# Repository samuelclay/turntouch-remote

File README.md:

# Turn Touch remote firmware, schematic, and board layout
> The design files used for the nrf51-based Turn Touch remote.

<a href="https://turntouch.com"><br />Available at turntouch.com</a>

[![License][license-image]][license-url]

## Screenshots of the board design files

| PCB | EAGLE |
|:---:|:---:|
|  |  |

| Top | Bottom |
|:---:|:---:|
|  |  |

## Background

You can read the complete documentation and background on the [Turn Touch blog series](http://ofbrooklyn.com/2019/01/3/building-turntouch/#firmware).

## Features of the remote

[Turn Touch](https://turntouch.com) is a smart home remote control carved out of beautiful mahogany wood. This is a remote control for Hue lights, Sonos speakers, and all the other connected devices in your home. Turn Touch works on iOS and macOS, giving you control of your music, videos, presentations, and more. 

- [x] **Extraordinary design**: This isn't yet another plastic remote. Turn Touch is carved from solid wood and worked to a show-stopping, textured finish. 
- [x] **Well connected**: Turn Touch connects to most smart devices in your home that speak WiFi. And this is just the first version. Over time, there's no telling what you'll be able to control.
- [x] **Always ready**: Turn Touch is always on, always connected, and always ready to take your breath away. Once you connect your Turn Touch via Bluetooth it stays connected and always available, even without the Turn Touch app actively running. And there's no delay, when you press a button the result is instant.
- [x] **Built to last**: Not only will your Turn Touch stand up to drops and shock — its entire circuit board can be inexpensively replaced with newer, future wireless tech. You won't have to buy a new remote every time Apple comes out with a new phone. And instead of flimsy plastic clasps, a set of 8 strong magnets invisibly hold the remote together. 

## Requirements

- macOS or Windows
- nrf51 Development Kit ([$39 on Digikey](https://www.digikey.com/product-detail/en/nordic-semiconductor-asa/NRF51-DK/1490-1038-ND/5022449))
- EAGLE for schematic and board layout
- ARM toolchain for firmware

## Installation

To install dependencies, start here:

    https://devzone.nordicsemi.com/blogs/22/getting-started-with-nrf51-development-on-mac-os-x/

To use gcc, you will need to download:

 * nRF51 SDK
 * S110 SoftDevice
 * J-Link by Segger
 * srec_cat

    ```$ brew install srecord```

 * GCC ARM Embedded

    When installing GCC tools, do not use "The Unarchiver". It messes up the symlinks for
    all of the binaries. Make sure to use "Archive Utility"
    ```
    $ mv -f ~/Downloads/gcc-arm-none-eabi-4_9-2015q2 ~/projects/code/
    $ ln -s ~/projects/code/gcc-arm-none-eabi-4_9-2015q2 /usr/local/gcc-arm-none-eabi-4_9-2015q2
    ```

 * ./bin/nrfjprog.sh into /usr/local/bin/nrfjprog

### Running

    $ make
    $ make bootloader
    $ make flash
    $ ./bin/nrfjprog.sh --rtt

### Build on Windows

#### Build DFU package

    $ C:\Keil_v5\ARM\ARMCC\bin\fromelf.exe --bin --output Z:\remote\ble_peripheral\ble_app_template\pca10028\s110\arm5\_build\nrf51422_xxac_s110.bin Z:\remote\ble_peripheral\ble_app_template\pca10028\s110\arm5\_build\nrf51422_xxac_s110.axf

    $ & 'C:\Program Files (x86)\Nordic Semiconductor\Master Control Panel\3.10.0.14\nrf\nrfutil.exe' dfu genpkg --sd-req 0xfffe --application Z:\remote\ble_peripheral\ble_app_template\pca10028\s110\arm5\_build\nrf51422_xxac_s110.bin --application-version 0x06 --dev-revision 0x01 Z:\remote\ble_peripheral\nrf51_06.zip

##### Back on Mac

    $ cp ../ble_peripheral/nrf51_*.zip ../../app/Turn\ Touch\ Mac/DFU/firmwares/
    $ cp ../ble_peripheral/nrf51_*.zip ../../ios/Turn\ Touch\ iOS/DFU/

##### In Xcode (in both turntouch-mac/turntouch-ios repos)

In Supporting Files/defaults.plist, change `TT:firmware:version`

#### Build flash hex

    $ mergehex -m Z:/remote/firmware/libs/components/softdevice/s110/hex/s110_nrf51_8.0.0_softdevice.hex Z:/remote/ble_peripheral/dfu/bootloader/pca10028/dual_bank_ble_s110/arm5/_build/nrf51422_xxac.hex Z:/remote/ble_peripheral/ble_app_template/pca10028/s110/arm5/_build/nrf51422_xxac_s110.hex -o Z:/remote/ble_peripheral/nrf51_sd_bootloader_app.hex

#### `make flashwin` on Mac in firmware/

### Upgrading to latest nrf51 SDK

 1) Replace app_error.c with RTT logs
 2) Add BSP_BUTTON_ACTION_LONG_PUSH and BSP_BUTTON_ACTION_RELEASE to bsp.c

## Contribute

We would love you for the contribution to the **Turn Touch remote firmware**. Feel free to submit a Pull Request with the improvements or additions you've made.

## Turn Touch open source repositories and documentation

Everything about Turn Touch is open source and well documented. Here are all of Turn Touch's repos:

* [Turn Touch Mac OS app](https://github.com/samuelclay/turntouch-mac/)
* [Turn Touch iOS app](https://github.com/samuelclay/turntouch-ios/)
* [Turn Touch remote firmware and board layout](https://github.com/samuelclay/turntouch-remote/)
* [Turn Touch enclosure, CAD, and CAM](https://github.com/samuelclay/turntouch-enclosure/)

The entire Turn Touch build process is also documented:
* <a href="http://ofbrooklyn.com/2019/01/3/building-turntouch/">Everything you need to build your own Turn Touch smart remote<br /></a>
* <a href="http://ofbrooklyn.com/2019/01/3/building-turntouch/#firmware">Step one: Laying out the buttons and writing the firmware <br /></a>
* <a href="http://ofbrooklyn.com/2019/01/3/building-turntouch/#cad">Step two: Designing the remote to have perfect button clicks <br /></a>
* <a href="http://ofbrooklyn.com/2019/01/3/building-turntouch/#cnc">Step three: CNC machining and fixturing to accurately cut wood <br /></a>
* <a href="http://ofbrooklyn.com/2019/01/3/building-turntouch/#laser">Step four: Inlaying the mother of pearl <br /></a>

## Author

Samuel Clay – [@samuelclay](https://twitter.com/samuelclay) – [samuelclay.com](http://samuelclay.com)

Distributed under the MIT license. See ``LICENSE`` for more information.

[https://github.com/samuelclay/turntouch-mac](https://github.com/samuelclay)

[swift-image]:https://img.shields.io/badge/swift-3.0-orange.svg
[swift-url]: https://swift.org/
[license-image]: https://img.shields.io/badge/License-MIT-blue.svg
[license-url]: LICENSE
[travis-image]: https://img.shields.io/travis/dbader/node-datadog-metrics/master.svg?style=flat-square
[travis-url]: https://travis-ci.org/dbader/node-datadog-metrics
[codebeat-image]: https://codebeat.co/badges/c19b47ea-2f9d-45df-8458-b2d952fe9dad
[codebeat-url]: https://codebeat.co/projects/github-com-vsouza-awesomeios-com

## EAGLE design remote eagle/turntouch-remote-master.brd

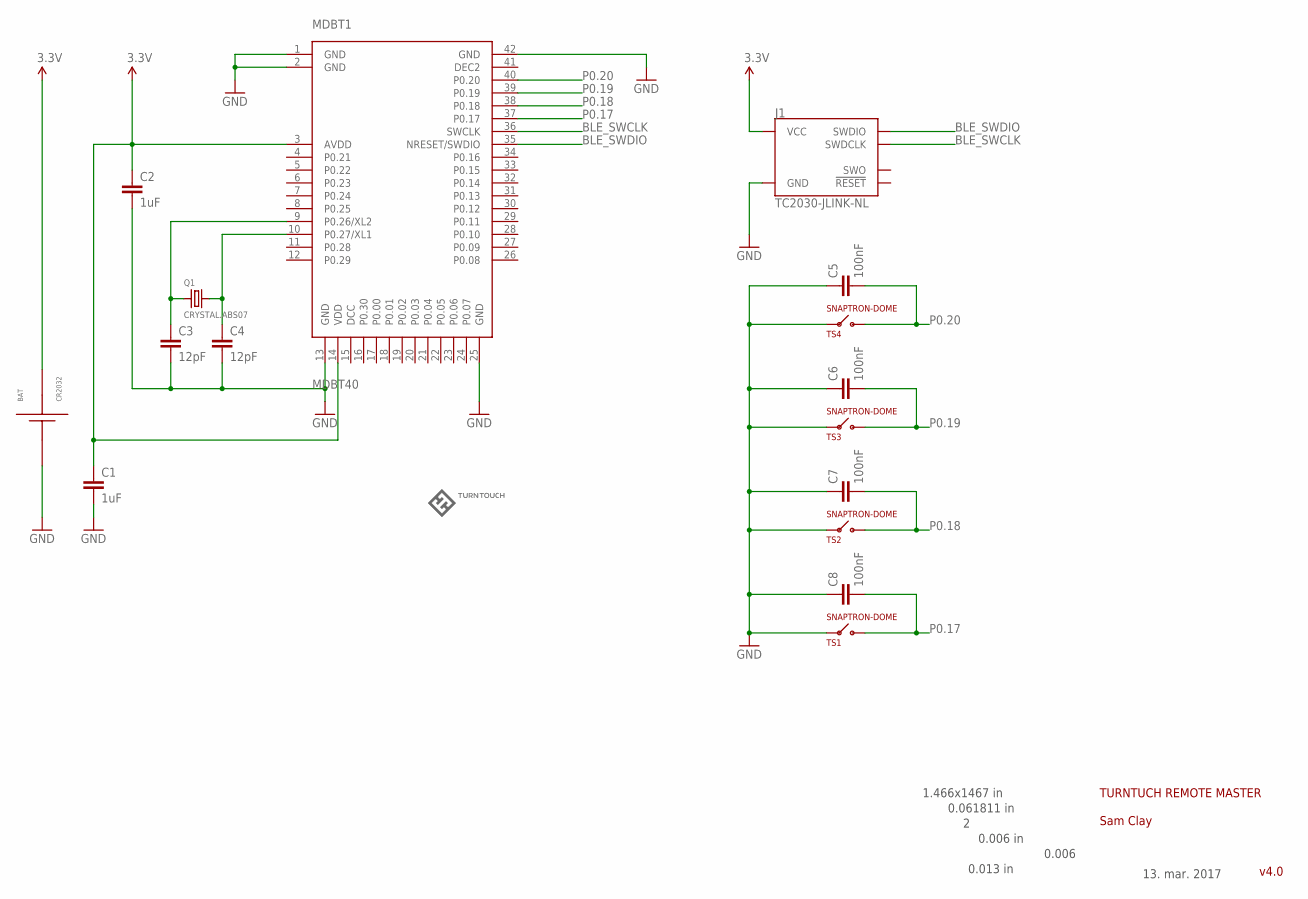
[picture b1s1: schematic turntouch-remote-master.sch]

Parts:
BAT: CR2032
C1, C2: 1uF; 0603-CAP
C3, C4: 12pF; 0603-CAP
C5, C6, C7, C8: 100nF; 0603-CAP
J1: TC2030-JLINK-NL; TC2030-IDC-NL
LOGO: TURNTOUCHLOGO200DPI; LOGO
MDBT1: MDBT40
Q1: CRYSTAL.ABS07; ABS07
TS1, TS2, TS3, TS4: SNAPTRON-DOME; DOME-M-SERIES

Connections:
3.3V: BAT.P$1 (VBAT), BAT.P$2 (VBAT), C1.1, C2.1, J1.1 (VCC), MDBT1.3 (AVDD), MDBT1.14 (VDD)
BLE_SWCLK: J1.4 (SWDCLK), MDBT1.36 (SWCLK)
BLE_SWDIO: J1.2 (SWDIO), MDBT1.35 (NRESET/SWDIO)
C5: C4.1, MDBT1.10 (P0.27/XL1), Q1.2
GND: BAT.GND, C1.2, C2.2, C3.2, C4.2, C5.1, C6.1, C7.1, C8.1, J1.5 (GND), MDBT1.1 (GND), MDBT1.2 (GND), MDBT1.13 (GND), MDBT1.25 (GND), MDBT1.42 (GND), TS1.P$1 (V), TS1.P$2 (V), TS2.P$1 (V), TS2.P$2 (V), TS3.P$1 (V), TS3.P$2 (V), TS4.P$1 (V), TS4.P$2 (V)
unnamed: C3.1, MDBT1.9 (P0.26/XL2), Q1.1
P0.17: C8.2, MDBT1.37 (P0.17), TS1.P$3 (B)
P0.18: C7.2, MDBT1.38 (P0.18), TS2.P$3 (B)
P0.19: C6.2, MDBT1.39 (P0.19), TS3.P$3 (B)
P0.20: C5.2, MDBT1.40 (P0.20), TS4.P$3 (B)

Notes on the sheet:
1.466x1467 in
0.061811 in
0.006 in
0.006
0.013 in
TURNTUCH REMOTE MASTER
v4.0
13. mar. 2017
Sam Clay

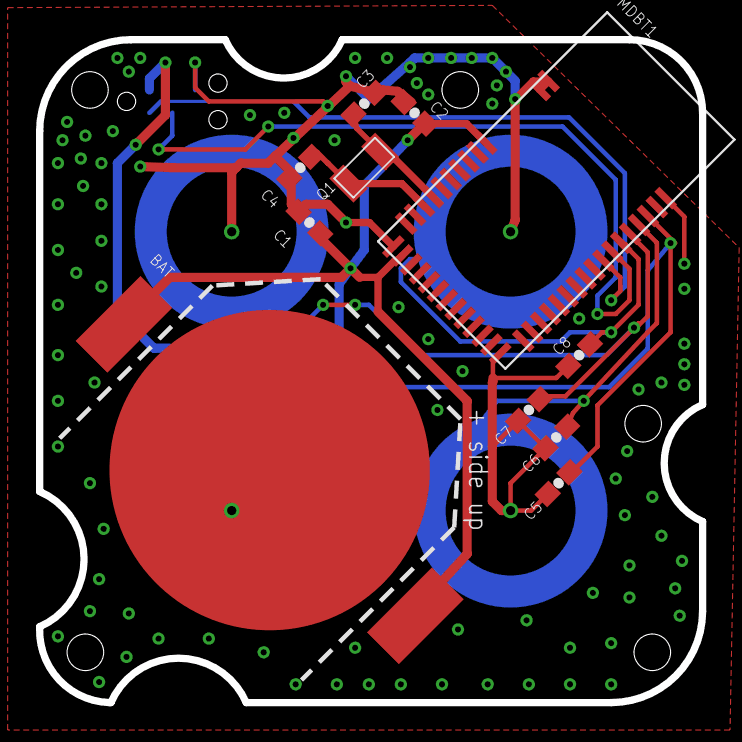
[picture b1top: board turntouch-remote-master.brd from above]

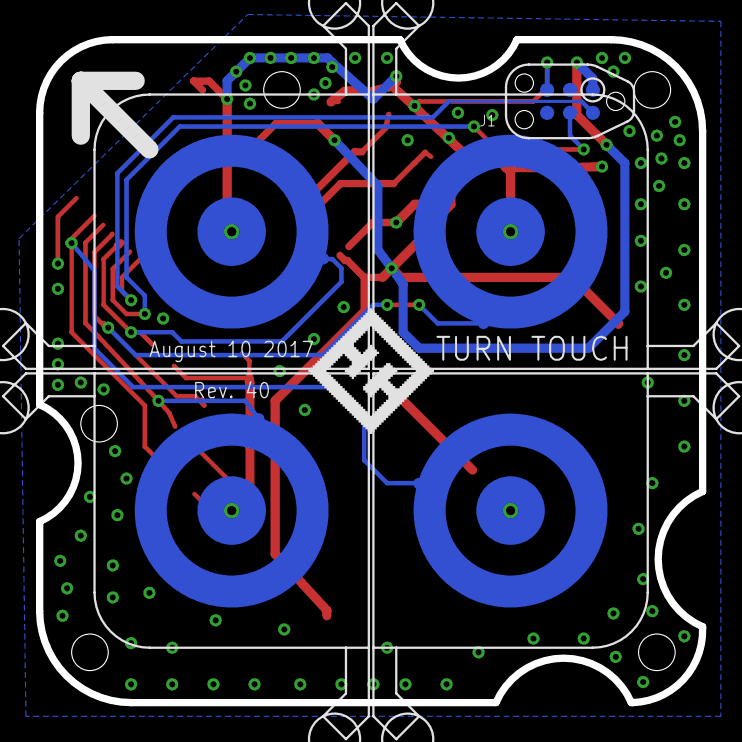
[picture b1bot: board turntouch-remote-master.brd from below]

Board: 2 copper layers, 36.8 x 36.8 mm, 17 parts (6 on the bottom side), 10 nets.

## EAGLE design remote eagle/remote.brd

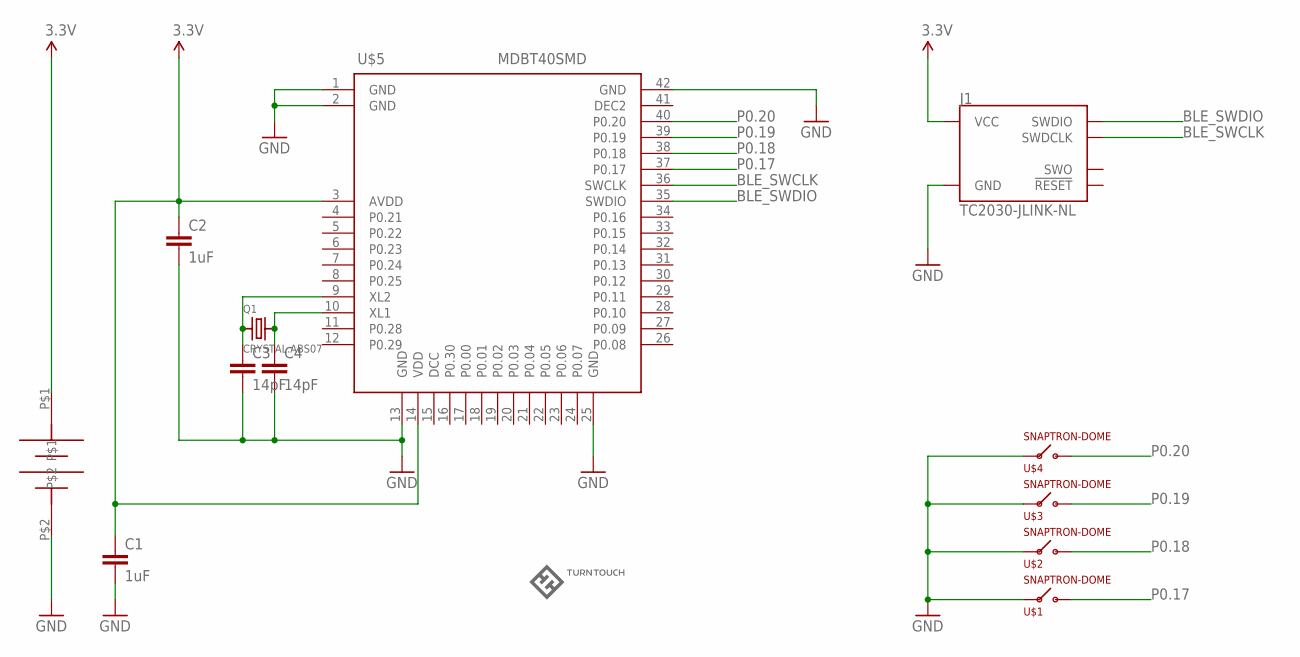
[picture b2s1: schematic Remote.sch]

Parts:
C1, C2: 1uF; 0603-CAP
C3, C4: 14pF; 0603-CAP
J1: TC2030-JLINK-NL; TC2030-IDC-NL
LOGO: TURNTOUCHLOGO200DPI; LOGO
Q1: CRYSTAL.ABS07; ABS07
U$1, U$2, U$3, U$4: SNAPTRON-DOME; DOME-M-SERIES
U$5: MDBT40SMD; MDBT40
U$6: COINCELLHOLDER; 20MMCOINCELL

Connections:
3.3V: C1.1, C2.1, J1.1 (VCC), U$5.3 (AVDD), U$5.14 (VDD), U$6.P$1
BLE_SWCLK: J1.4 (SWDCLK), U$5.36 (SWCLK)
BLE_SWDIO: J1.2 (SWDIO), U$5.35 (SWDIO)
C5: C4.1, Q1.2, U$5.10 (XL1)
GND: C1.2, C2.2, C3.2, C4.2, J1.5 (GND), U$1.P$1 (V), U$1.P$2 (V), U$2.P$1 (V), U$2.P$2 (V), U$3.P$1 (V), U$3.P$2 (V), U$4.P$1 (V), U$4.P$2 (V), U$5.1 (GND), U$5.2 (GND), U$5.13 (GND), U$5.25 (GND), U$5.42 (GND), U$6.P$2
unnamed: C3.1, Q1.1, U$5.9 (XL2)
P0.17: U$1.P$3 (B), U$5.37 (P0.17)
P0.18: U$2.P$3 (B), U$5.38 (P0.18)
P0.19: U$3.P$3 (B), U$5.39 (P0.19)
P0.20: U$4.P$3 (B), U$5.40 (P0.20)

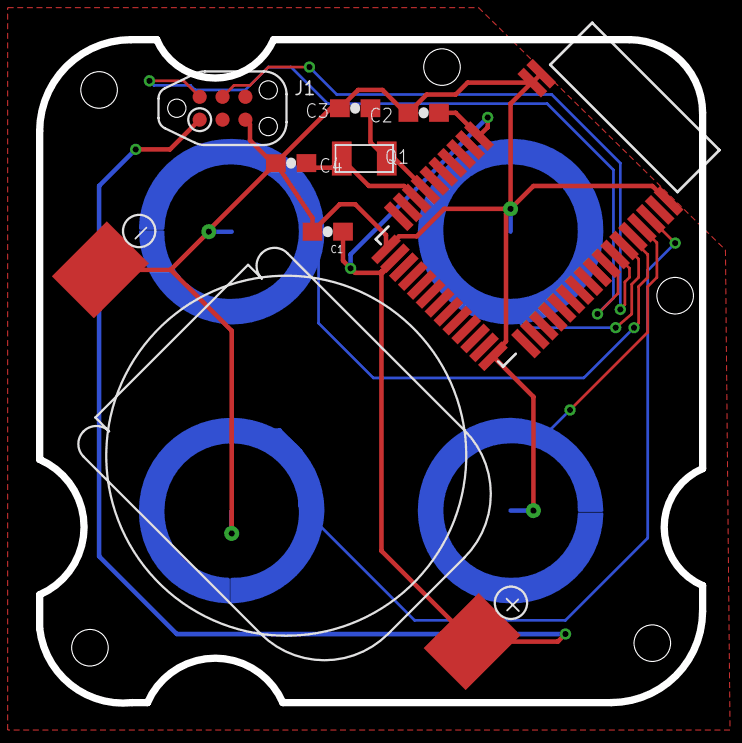
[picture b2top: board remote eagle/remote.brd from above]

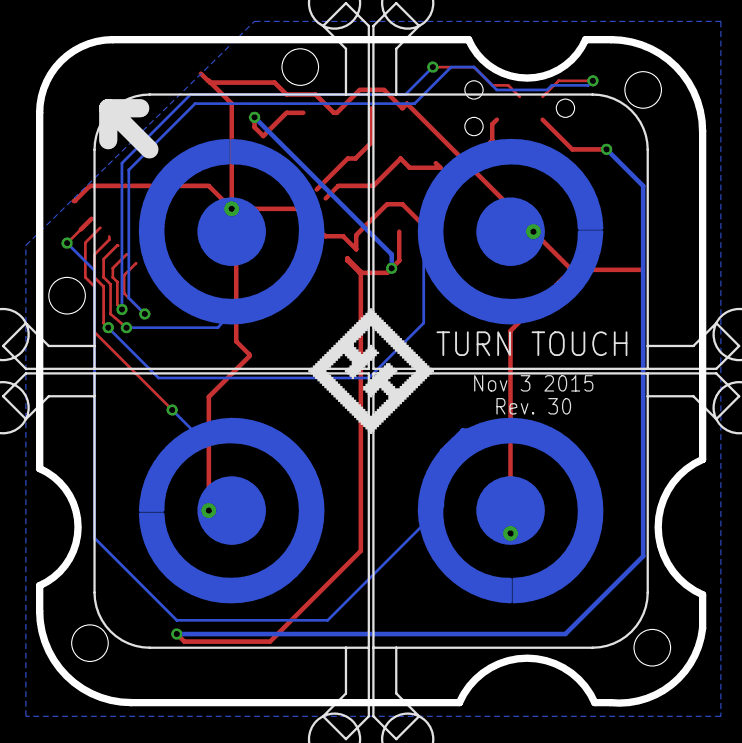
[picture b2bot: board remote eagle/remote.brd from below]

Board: 2 copper layers, 36.8 x 36.9 mm, 13 parts (5 on the bottom side), 10 nets.

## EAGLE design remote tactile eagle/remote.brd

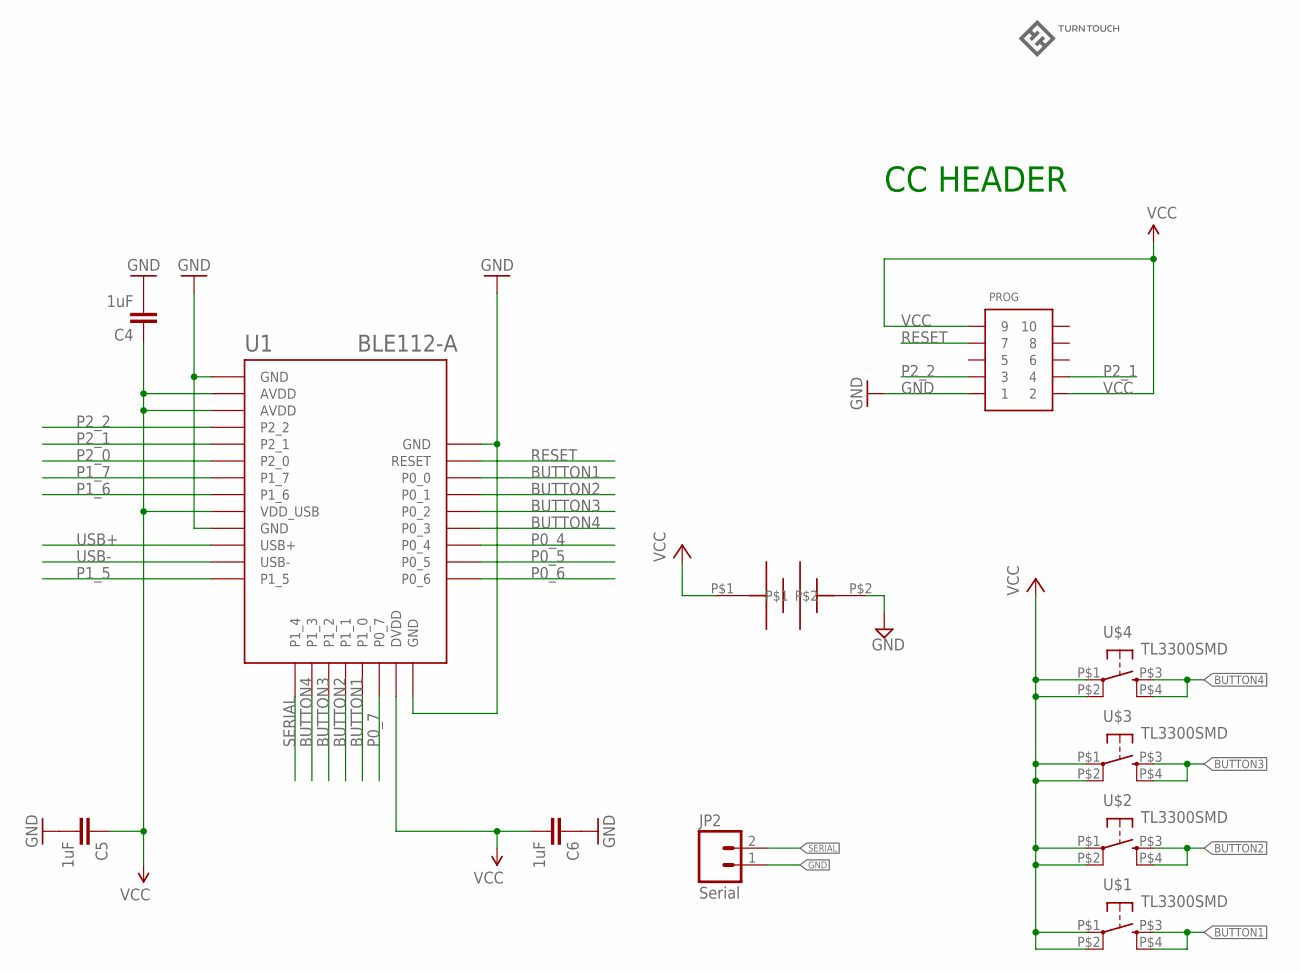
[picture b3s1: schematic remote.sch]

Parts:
C4, C5, C6: 1uF; 0603-CAP
JP2: Serial; 1X02
LOGO: TURNTOUCHLOGO200DPI; LOGO
PROG: CONN_5-2-FTSH-V; FTSH-105-DV
U1: BLE112-A
U$1, U$2, U$3, U$4: TL3300SMD; TL3300
U$6: COINCELLHOLDER; 20MMCOINCELL

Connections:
BUTTON1: U1.P0_0, U1.P1_0, U$1.P$3 (S), U$1.P$4 (S1)
BUTTON2: U1.P0_1, U1.P1_1, U$2.P$3 (S), U$2.P$4 (S1)
BUTTON3: U1.P0_2, U1.P1_2, U$3.P$3 (S), U$3.P$4 (S1)
BUTTON4: U1.P0_3, U1.P1_3, U$4.P$3 (S), U$4.P$4 (S1)
GND: C4.2, C5.2, C6.1, JP2.1, PROG.1, U1.GND1 (GND), U1.GND2 (GND), U1.GND3 (GND), U1.GND4 (GND), U$6.P$2
P0_4: U1.P0_4
P0_5: U1.P0_5
P0_6: U1.P0_6
P0_7: U1.P0_7
P1_5: U1.P1_5
P1_6: U1.P1_6
P1_7: U1.P1_7
P2_0: U1.P2_0
P2_1: PROG.4, U1.P2_1
P2_2: PROG.3, U1.P2_2
RESET: PROG.7, U1.RESET
SERIAL: JP2.2, U1.P1_4
USB+: U1.USB+
USB-: U1.USB-
VCC: C4.1, C5.1, C6.2, PROG.2, PROG.9, U1.AVDD1 (AVDD), U1.AVDD2 (AVDD), U1.DVDD, U1.VDD_USB, U$1.P$1, U$1.P$2 (P1), U$2.P$1, U$2.P$2 (P1), U$3.P$1, U$3.P$2 (P1), U$4.P$1, U$4.P$2 (P1), U$6.P$1

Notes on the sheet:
CC HEADER

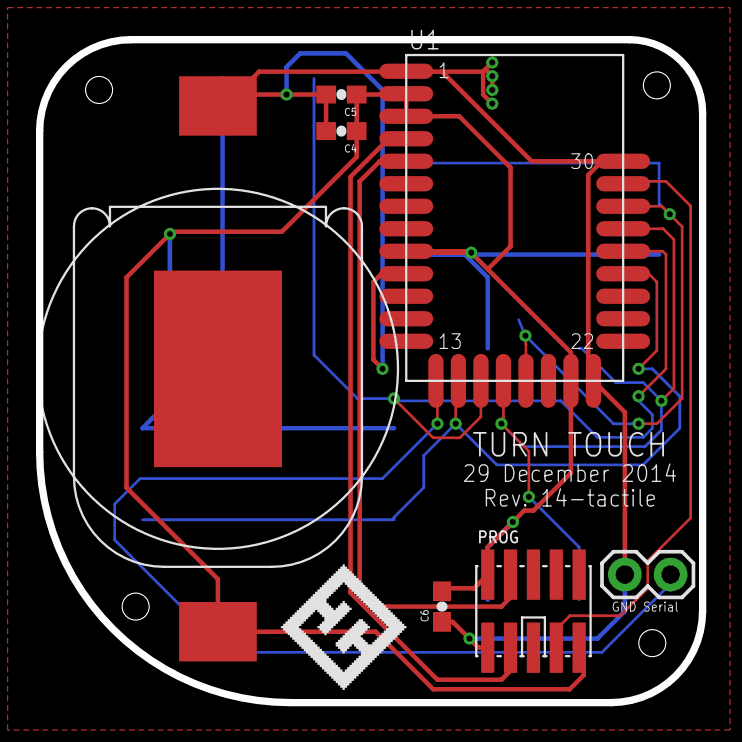
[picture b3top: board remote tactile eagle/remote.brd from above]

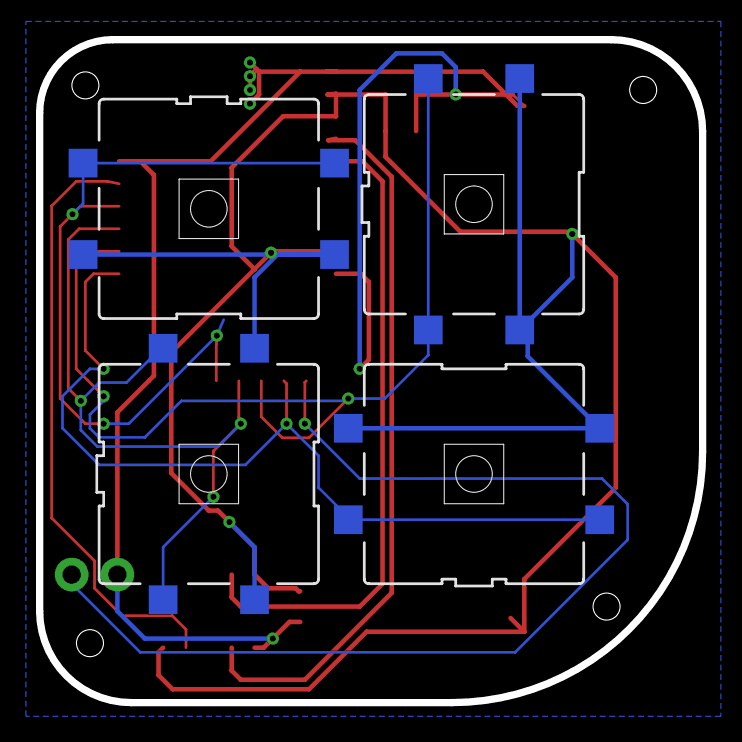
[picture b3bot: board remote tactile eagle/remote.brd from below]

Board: 2 copper layers, 36.8 x 36.8 mm, 12 parts (4 on the bottom side), 10 nets.

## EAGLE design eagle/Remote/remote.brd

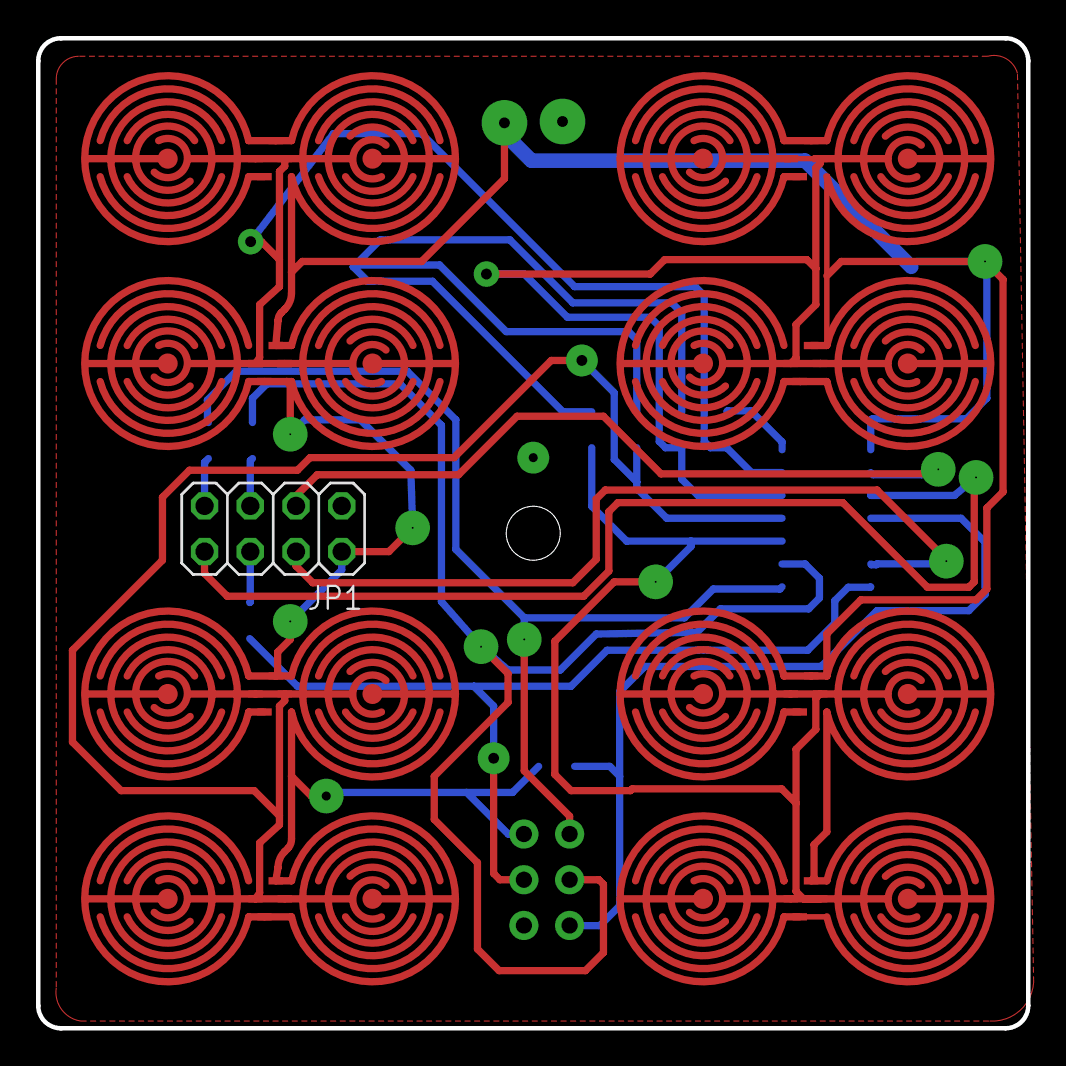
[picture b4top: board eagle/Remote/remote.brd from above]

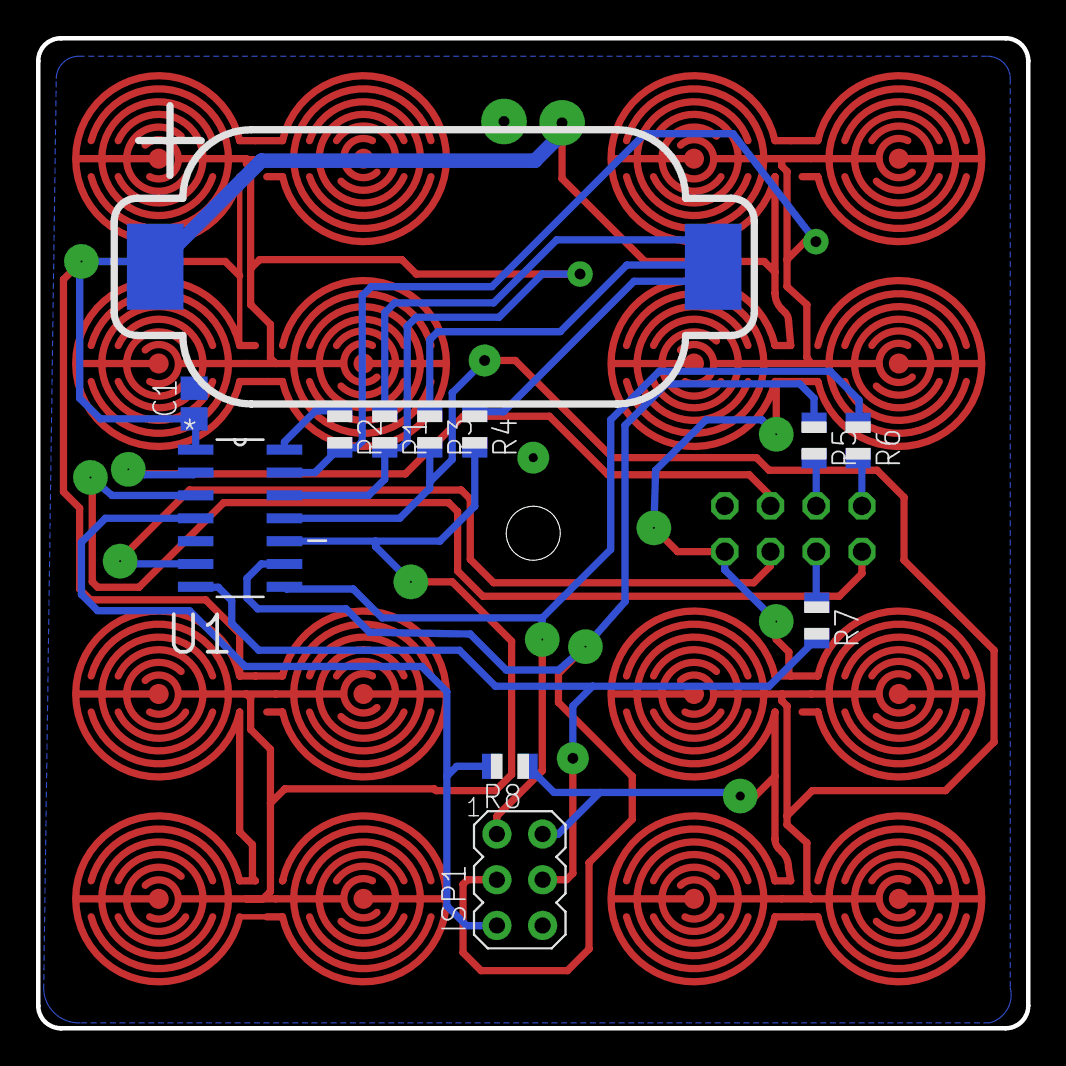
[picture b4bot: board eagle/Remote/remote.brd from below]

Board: 2 copper layers, 55.0 x 55.0 mm, 29 parts (12 on the bottom side), 16 nets.

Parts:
BUTTON1-A, BUTTON1-B, BUTTON1-C, BUTTON1-D, BUTTON2-A, BUTTON2-B, BUTTON2-C, BUTTON2-D, BUTTON3-A, BUTTON3-B, BUTTON3-C, BUTTON3-D, BUTTON4-A, BUTTON4-B, BUTTON4-C, BUTTON4-D: BUTTON-25MM-4PAD
C1: .1uf; C0805
ISP1: AVRISP-6; AVRISP
JP1: 2X04
R1, R2, R3, R4: R0805
R5, R7, R8: 10k; R0805
R6: 10K; R0805
U1: ATTINY84-20SSU; SOIC127P600X175-14N
U$1: A99327CT-ND

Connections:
BUTTON1: BUTTON1-A.P$2, BUTTON1-B.P$2, BUTTON1-C.P$2, BUTTON1-D.P$2, R2.2, U1.13
BUTTON2: BUTTON2-A.P$2, BUTTON2-B.P$2, BUTTON2-C.P$2, BUTTON2-D.P$2, R1.2, U1.12
BUTTON3: BUTTON3-A.P$2, BUTTON3-B.P$2, BUTTON3-C.P$2, BUTTON3-D.P$2, R3.2, U1.11
BUTTON4: BUTTON4-A.P$2, BUTTON4-B.P$2, BUTTON4-C.P$2, BUTTON4-D.P$2, R4.2, U1.10
CE: JP1.3, U1.2
CSN: JP1.4, U1.6
GND: C1.2, ISP1.6, JP1.1, R1.1, R2.1, R3.1, R4.1, U1.14, U$1.P$2
IRQ: JP1.8, U1.3
MISO: ISP1.1, R6.1, U1.8
MOSI: ISP1.4, R7.2, U1.7
unnamed: JP1.5, R5.2
unnamed: JP1.7, R6.2
unnamed: JP1.6, R7.1
RESET: ISP1.5, R8.2, U1.4
SCK: ISP1.3, R5.1, U1.9
VCC: BUTTON1-A.P$1, BUTTON1-B.P$1, BUTTON1-C.P$1, BUTTON1-D.P$1, BUTTON2-A.P$1, BUTTON2-B.P$1, BUTTON2-C.P$1, BUTTON2-D.P$1, BUTTON3-A.P$1, BUTTON3-B.P$1, BUTTON3-C.P$1, BUTTON3-D.P$1, BUTTON4-A.P$1, BUTTON4-B.P$1, BUTTON4-C.P$1, BUTTON4-D.P$1, C1.1, ISP1.2, JP1.2, R8.1, U1.1, U$1.P$1

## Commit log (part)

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2013-08-02 Basic control circuit. Has four leds, four toggles, and logic to move between modes and blink on hits.
2013-10-30 Single button radio remote. Needs interrupts for low power.
2013-11-01 Using pullup resistros instead of pulldown.
2013-11-06 Adding receiver eagle files.
2013-11-15 update schematic and implement board
2013-12-02 Separating remote and receiver.
2013-12-09 Adding pin change interface, but it doesn't work for 1/4 pins. Adding serial debugger back in.
2013-12-10 Fixing broken interrupt. Turns out the pin change library was artificially limiting the PCINTs to 3.
2013-12-17 lowercasing
2013-12-18 Removing .d files. Also switching to locally vendorized avr library.
2013-12-18 Assignment change.
2014-01-15 Updating remote schematic to include new crystal.
2014-01-24 Final placement of components. Needs lots of electrical wiring.
2014-01-24 Finishing up electrical connections. Replacing battery holder with double-pronged sides.
2014-03-12 Fixing remote issues with serial monitor.
2014-03-14 Re-laying out the board for the third revision. This one has correct wiring, less expensive crystal, and components in more logical places. Could use some contact points.
2014-04-04 New reduced size (1.44" square) board layout.
2014-04-25 Fixing up board.
2014-04-25 Debouncing buttons. Works incredibly well now.
2014-05-06 Rev. 5, includes new isp touch.
2014-06-05 Adding script for bitmap conversions for the logo.
2014-07-28 Moving code into src/ and libs/.
2014-07-29 Correctly sending and receiving. Time to merge.
2014-07-31 Adding auto-ack.
2014-07-31 Adding addressing.
2014-09-10 Beginning rerouting for new battery holder.
2014-09-30 Adding skeleton enclosure.
2014-10-01 Drawing skeleton top of enclosure, aligning.
2014-10-02 Guidelines for buttons.
2014-10-02 Button cover needs a latch.
2014-10-02 Moving from M4x.7 to M2x.4 screws
2014-10-08 Adding IDF model.
2014-10-18 Switching from nRF24L01 to RFM22B wireless module.
2014-10-20 Fixing speed issues, turning sleep back on.
2014-10-22 Revision 12 of the board, complete with RFM22B RF module.
2014-11-08 Revision 13, with new snaptron dome buttons.
2014-11-20 New Rhino-ified remote enclosure has four buttons and a top. Just need bottom, screw holes, and bracketing.
2014-11-21 Enclosure just needs holes on bottom, cut supports, and a filled in side.
2014-11-24 Filling in sides of enclosure. Also adding screw holes on bottom. Realigning screw holes.
2014-11-24 Three pieces sent for printing: top, bottom, buttons.
2014-12-04 Widening microstrip to as wide as possible.
2014-12-20 Attaching rising and falling edge detections on pins 0-3 on both port 1 and 0.
2014-12-21 Debouncing both rising and falling of buttons.
2014-12-21 Adding mode change notification from remote.
2014-12-22 Fixing bug where remote would stop trying to connect if a button was pushed while disconnected.
2014-12-22 Adding BLE112/Bluegiga library for eagle.
2014-12-23 Stubbing in rev14 of enclosure. Needs pcb brackets, top push down brackets and latches, and buttons.
2014-12-24 4 buttons in a block. Need to bend the junction when the top/sides are built.
2014-12-25 Splitting sides, adding grove to connect them back. Just needs cleanup and its ready to go for printing.
2014-12-25 Revision 14 of the enclosure (3rd enclosure revision).
2014-12-30 Adding tactile version of rev. 14 of board, for use without enclosure.
2015-01-16 Updating buttons for new, smaller enclosure. Also adding them to blocks. Just need to split the enclosure and snap it back together.
2015-01-17 Finishing up remote enclosure. Button's need nub extracted ontop top layer.
2015-01-22 Adding battery level status characteristic and service. Only updates when battery level goes down (except it's in debug mode right now, so it constantly fires).
2015-02-05 Flipping buttons from active HIGH to active LOW. Required a lot of fiddling.
2015-02-06 Completed rev 16 of the enclosure. Better latches, fixed PCB brackets.
2015-02-06 Exporting rev 16 of remote enclosure. Moving from OBJ to STL files.
2015-02-28 Adding 0.1mm height to enclosure. Redrawing latches to be locked in xyz, not just zy. No longer chopping off bottom of remote.
2015-03-02 Adding combined buttons STL, since it's cheaper to just print all four buttons at once instead of 4 x button.
2015-03-06 Adding locking latch to northeast side of enclosure. Ready to print.
2015-03-17 Updating schematic and adding new .STP renders.
2015-03-18 Adding logo and turn touch emboss to bottom. Adding star to orient inside bottom. Raising north ridge on top.
2015-03-19 Lower connection latency to prevent bluetooth disconnects (as per spec). Raising interval to compensate.
2015-03-24 Revision 18. Adding south dual-holes for orientation.
2015-04-01 Revision 18 of enclosure. Has north button bowl, 5 brackets for pcb, logo on bottom.
2015-04-03 Aligning brackets and submitting to shapeways.
2015-04-07 New config.xml file for handling ps store size.
2015-04-08 Extracting sleep procedure. Commenting. Adding Flash ps saves when server posts new attribute values.
2015-04-08 Moving firmware setting characteristics to their own service.
2015-04-17 Redrawing button faces so they are equal and have 0.008" space between them.
2015-04-18 Adding two north button ridges. Need to taper the edges on both.
2015-04-19 Cleaning up layers.
2015-05-07 Remodeling top and bottom side case to be even and uniform.
2015-05-12 ps_error is 0384 when there's no default, so don't worry about it.
2015-05-16 Reformed model for smooth edges. This may be the final remote for the first prototype batch.
2015-05-19 Singularizing models, switching out button connector from pyramids to rods.
2015-05-22 Fattening connectors for printing 4x remotes at a time.
2015-06-04 Moving to solidworks. New remote assembly.
2015-06-06 Revision 19 of the pcb, shaped to fit revision 9 of the enclosure (solidworks).
2015-06-09 Preparing assembly for printing.
2015-06-09 STLs.
2015-06-14 Deleting unused parts and assemblies.
2015-06-16 Stubbing in nrf51 firmware.
2015-06-16 Taking nrf51 SDK out of source tree.
2015-06-17 Adding separate buttons, extracting out curves from top to make buttons.
2015-06-18 Adding remote buttons export for exporting just the buttons (and not the derived sketch of the top).
2015-06-19 Adding PCB, adding mounts to bottom for PCB. Also adding lip to top and bottom.
2015-06-20 Adding turn touch logo. All done! Sending to printer.
2015-06-23 STL for buttons ensured in inches.
2015-06-23 Removing build folder.
2015-06-24 Turning LEDs on and off based on button press, hold, and release.
2015-06-24 Fixing bluetooth (just needed to flash softdevice).
2015-06-25 Adding button service and button status characteristic and firmware nickname characteristic. Both stubbed in. Getting an error on advertisement init.
2015-06-26 Fixing rev 19's flaws.
2015-06-27 Revision 20 of the pcb. Includes new 6-pin tag connect and nRF51822 Seeed bluetooth module.
2015-06-27 Adding doc images of tag connect and programmer pinouts.
2015-06-30 Revision 20 of the enclosure. North ridge needs love, but otherwise should be good.
2015-07-01 Fixing revision 20 of buttons. Adding print joiner.
2015-07-01 Correctly sending mode change in notification packet.
2015-07-02 Adding device manager for handling pstorage. Still not entirely sure how it works, but if bonding info is cleared then it doesn't connect.
2015-07-08 Allowing long writes of firmware nickname gatt value. Still need to copy client's written nickname into pstorage and then retrieve it.
2015-07-08 Cleaning up.
2015-07-08 Adding implicit func declarations.
2015-07-09 Looking like the remote works again. Nickname saved (although potentially cut off?)
2015-07-14 Adding battery level measurement. Adding GPIO interrupts and sleeping. Adding custom board config.
2015-07-15 Adding extra corners for snap fit connectors. Beginning to redraw snap fits to accomodate rectangular shape instead of circular shape.
2015-07-16 Revision 21 of enclosure. New round snap fit connectors, added 2 for a total of 6 connectors.
2015-07-16 Fixing buttons for export rev 21.
2015-07-18 Adding Case Bottom with tabs and tab indents on remote bottom.
2015-07-22 Cleaning up case top/bottom.
2015-07-23 Shuffling around enclosure files.
2015-07-28 Revision 22 of enclosure. Removing oldversions.
2015-08-04 Adding logo to be engraved. Also finalizing bits. Just need to draw t-slot undercutting traces.
2015-08-06 Fixing Case Bottom's mating tabs to fit below the border. Re-doing CAM for top of bottom case.
2015-08-06 Updating assembly with fixed bottom.
2015-08-06 Finishing CAM on case bottom. Now need to replace button pegs.
2015-08-07 Redrawing north ridge on case buttons and removing broken north ridge from remote buttons.
2015-08-08 Revision 23 of enclosure and case. Sending to printer.
2015-08-10 Moving enclosure to samuelclay/turntouch-enclosure.
2015-08-20 added pstorage code
2015-08-21 Sticking bootloader on same hex as app. Still doesn't restart into DFU mode properly, though.
2015-08-24 Revision 24 of board. Now uses MDBT40 module.
2015-08-25 Correctly setting button status service's firmware nickname characteristic correctly based on pstorage.
2015-08-27 Updating readme.
2015-08-27 Attempting to make bootloader debugable.
2015-08-27 Removing extra sdk.
2015-08-27 Updating bootloader to sdk 9.0.
2015-08-28 Adding ble template for Keil.
2015-08-28 Finally got the keil debugger worker. Now it looks like the timer is broken.
2015-09-03 Fixing longpress and button up on Keil-compiled remote. Looks like its done and now ready to work on DFU.
2015-09-04 Adding dfu bootloader to keil.
2015-09-16 Revision 28 of the board. Fixing VDD/GND mixup.
2015-10-09 Adding build directories.
2015-10-13 Reivison 29 of firmware (zip).
2015-10-14 Fixing gcc to auto-load the app when flashing bootloader + sd + app.
2015-10-21 Fixing buttons turning off during disconnection.
2015-10-29 Undoing button disabling in windows.
2015-10-30 Half of the traces for rev30.
2015-11-03 Partially laying out board.
2015-11-04 Revision 30 of the board. Moved the radio out a bit so the antenna has no PCB ground plane underneath. Also added an extra boss hole.
2015-11-12 Expanding bootloader, adding battery meter.
2015-11-13 Changing memory sizes to accomodate debugging.
2015-11-17 Upgrading to nrf51 SDK 10.0.
2015-11-17 Changing bootloader to debug.
2015-11-17 Archiving gcc sdk 9.0 firmware
2015-11-18 Moving into archive.
2015-11-18 Moving gcc bootloader.
2015-11-20 Fixing BSP in SDK 10.
2015-12-04 Adding BOM, although Google Docs has a better BOM.
2015-12-09 Adding restrict to snaptron dome layout between contacts. Also widening vent hole.
2015-12-14 Adding double-click handler (with early expiring app timer bug handled). Firmware v3.
2015-12-19 Removing Debug.
2015-12-27 v3 of the firmware.
2016-01-26 v4 - fixes device restart when holding down 3 or 4 buttons.
2016-03-29 Didnt do anything but build.
2016-04-21 Rewriting bootloader makefile to not have crappy line endings.
2016-04-21 upgrading arm build tools to 5.3.1. Also adjusting memory footprint of bootloader to fit.
2016-07-20 Mucking with the firmware bootloader memory settings without justification lead to brokenness. Reverting.
2016-12-14 Adding feature that sends the last button press if remote is unconnected and connects within 30 sec.
2016-12-14 Fixing typo.
2016-12-16 Getting the hang of bootloader memory settings. Now large enough to handle debugging, works for both windows/keil and gcc.
2016-12-26 Double click down to 300ms, adding erase to make flashall.
2017-03-06 Cleaning up clock on schematic.
2017-03-14 Rev 35 of remote board. Includes fixes for current consumption, button debouncing, and updated BOM.
2017-03-14 Updating rev 35 to move the peg so as not to interfere with the button arms.
2017-03-19 No debug log support.
2017-03-28 Rev 37. Moving a single mounting peg. Also rearranging a few ground vias.
2017-04-10 Revision 38. Just moving mounting pegs.
2017-05-16 Infinite slow advertisement.
2017-06-07 Adding metal domes to bom.
2017-08-11 New MDBT40 footprint. Rev 40.
2017-08-15 Adding TAG Connect just in case.
2017-08-15 Removing battery holder paste.
2017-09-05 Switching back to old nrfjprog.
2017-09-26 Latest gerbers for rev 40 (with fixed ground).
2017-12-19 Fixing RTT.
2019-01-04 Fixing title

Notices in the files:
parts and their libraries:
SparkFun-Capacitors: Licensing: CC v3.0 Share-Alike You are welcome to use this library for commercial purposes.
